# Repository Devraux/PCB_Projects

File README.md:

# PCB sample projects
This repository contains my PCB designs made in KiCad and Altium designer. 
In some cases there is no silkscreen - this is caused by our custom fabrication methods.
In some cases there are "huge" vias - this is caused by our custom(handmoade) fabrication via methods

# Signal Sniffer
|  |  |
|------------------------------------------------------------|-------------------------------------------------------------|
|  |  |

# STM32 Distance sensor
|  |  |
|------------------------------------------------------------|-------------------------------------------------------------|
|  |  |

# Analog multiplier
|  |  |
|------------------------------------------------------------|-------------------------------------------------------------|
|  |  |

# Clock buffer & signal translator
|  |  |
|------------------------------------------------------------|-------------------------------------------------------------|

# Raspberry Pi Pico PIO Signal sniffer
|  |  |
|------------------------------------------------------------|-------------------------------------------------------------|

# HDMI FPGA PMOD adapter
|  |  |
|------------------------------------------------------------|-------------------------------------------------------------|

# Raspberry Pi Pico - Digital probe with HDMI adapter
|  |  |
|------------------------------------------------------------|-------------------------------------------------------------|

|  |  |
|------------------------------------------------------------|-------------------------------------------------------------|

# FPGA ZYNQ Clock TDC
|  |  |
|------------------------------------------------------------|-------------------------------------------------------------|

|  |  |
|------------------------------------------------------------|-------------------------------------------------------------|

|  |  |
|------------------------------------------------------------|-------------------------------------------------------------|

# FPGA RJ11 adapter with RS232 translator
|  |  |
|------------------------------------------------------------|-------------------------------------------------------------|

# Clock signal splitter(2 x 12)
|  |  |
|------------------------------------------------------------|-------------------------------------------------------------|

|  |  |
|------------------------------------------------------------|-------------------------------------------------------------|

# Clock signal splitter(2 x 16)
|  |  |
|------------------------------------------------------------|-------------------------------------------------------------|

|  |  |
|------------------------------------------------------------|-------------------------------------------------------------|

|  |  |
|------------------------------------------------------------|-------------------------------------------------------------|

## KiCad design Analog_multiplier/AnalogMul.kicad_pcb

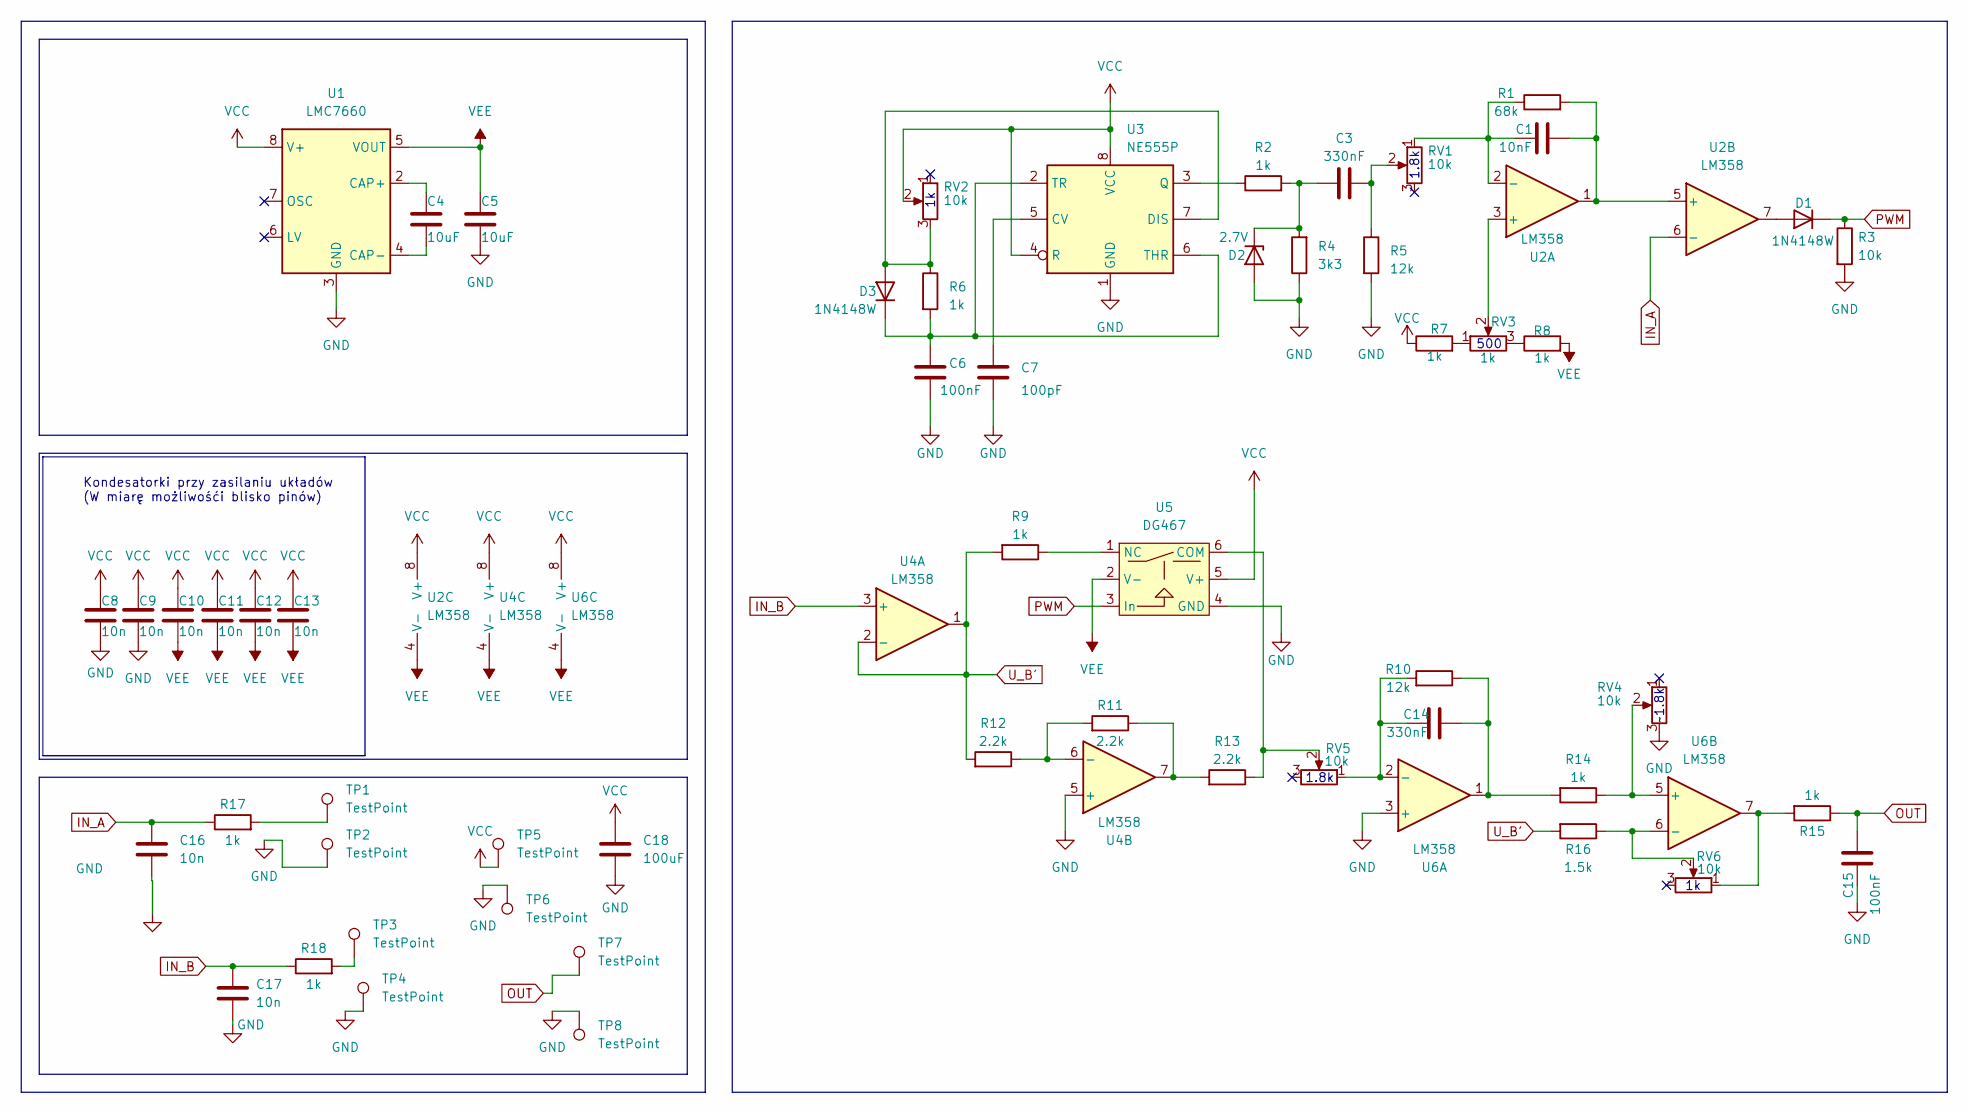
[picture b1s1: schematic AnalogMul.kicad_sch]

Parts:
C1: 10nF; C_0805_2012Metric_Pad1.18x1.45mm_HandSolder
C3, C14: 330nF; C_0805_2012Metric_Pad1.18x1.45mm_HandSolder
C4, C5: 10uF; C_1206_3216Metric
C6, C15: 100nF; C_0805_2012Metric_Pad1.18x1.45mm_HandSolder
C7: 100pF; C_0805_2012Metric_Pad1.18x1.45mm_HandSolder
C8, C9, C10, C11, C12, C13, C16, C17: 10n; C_0805_2012Metric_Pad1.18x1.45mm_HandSolder
C18: 100uF; C_1206_3216Metric
D1, D3: 1N4148W; D_SOD-523
D2: 2.7V; D_SOD-523
R1: 68k; R_0805_2012Metric_Pad1.20x1.40mm_HandSolder
R2, R6, R7, R8, R9, R14, R15, R17, R18: 1k; R_0805_2012Metric_Pad1.20x1.40mm_HandSolder
R3: 10k; R_0805_2012Metric_Pad1.20x1.40mm_HandSolder
R4: 3k3; R_0805_2012Metric_Pad1.20x1.40mm_HandSolder
R5, R10: 12k; R_0805_2012Metric_Pad1.20x1.40mm_HandSolder
R11, R12, R13: 2.2k; R_0805_2012Metric_Pad1.20x1.40mm_HandSolder
R16: 1.5k; R_0805_2012Metric_Pad1.20x1.40mm_HandSolder
RV1, RV2, RV4, RV5, RV6: 10k; Potentiometer_Runtron_RM-063_Horizontal
RV3: 1k; Potentiometer_Runtron_RM-063_Horizontal
TP1, TP2, TP3, TP4, TP5, TP6, TP7, TP8: TestPoint; TestPoint_Loop_D1.80mm_Drill1.0mm_Beaded
U1: LMC7660; SO-8_3.9x4.9mm_P1.27mm
U2, U4, U6: LM358; SO-8_3.9x4.9mm_P1.27mm
U3: NE555P; SO-8_3.9x4.9mm_P1.27mm
U5: DG467; SOT-23-6

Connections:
GND: C5.1, C6.2, C7.2, C8.2, C9.2, C15.1, C16.2, C17.1, C18.2, D2.2 (A), R3.2, R4.1, R5.2, RV4.3, TP2.1, TP4.1, TP6.1, TP8.1, U1.3 (GND), U3.1 (GND), U4.5 (+), U5.4 (GND), U6.3 (+)
IN_A: C16.1, R17.1, U2.6 (-)
IN_B: C17.2, R18.1, U4.3 (+)
unnamed: C3.2, R5.1, RV1.2
unnamed: C14.2, R10.1, R14.2, U6.1
unnamed: D1.2 (A), U2.7
unnamed: C3.1, D2.1 (K), R2.2, R4.2
unnamed: D3.2 (A), R6.1, RV2.3, U3.7 (DIS)
unnamed: C6.1, D3.1 (K), R6.2, U3.2 (TR), U3.6 (THR)
unnamed: R7.2, RV3.1
unnamed: R8.1, RV3.3
unnamed: R11.1, R13.2, U4.7
unnamed: R15.2, RV6.1, U6.7
unnamed: R17.2, TP1.1
unnamed: R18.2, TP3.1
unnamed: C4.1, U1.2 (CAP+)
unnamed: C4.2, U1.4 (CAP-)
unnamed: RV3.2, U2.3 (+)
unnamed: C1.1, R1.1, RV1.1, U2.2 (-)
unnamed: C1.2, R1.2, U2.1, U2.5 (+)
unnamed: C7.1, U3.5 (CV)
unnamed: R2.1, U3.3 (Q)
unnamed: R11.2, R12.1, U4.6 (-)
unnamed: R13.1, RV5.2, U5.6 (COM)
unnamed: R9.1, U5.1 (NC)
unnamed: C14.1, R10.2, RV5.1, U6.2 (-)
unnamed: R14.1, RV4.2, U6.5 (+)
unnamed: R16.1, RV6.2, U6.6 (-)
OUT: C15.2, R15.1, TP7.1
PWM: D1.1 (K), R3.1, U5.3 (In)
U_B': R9.2, R12.2, R16.2, U4.1, U4.2 (-)
VCC: C8.1, C9.1, C10.1, C11.1, C12.1, C13.1, C18.1, R7.1, RV2.2, TP5.1, U1.8 (V+), U2.8 (V+), U3.4 (R), U3.8 (VCC), U4.8 (V+), U5.5 (V+), U6.8 (V+)
VEE: C5.2, C10.2, C11.2, C12.2, C13.2, R8.2, U1.5 (VOUT), U2.4 (V-), U4.4 (V-), U5.2 (V-), U6.4 (V-)

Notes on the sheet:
~1.8k
Kondesatorki przy zasilaniu układów (W miarę możliwośći blisko pinów)
1.8k
500

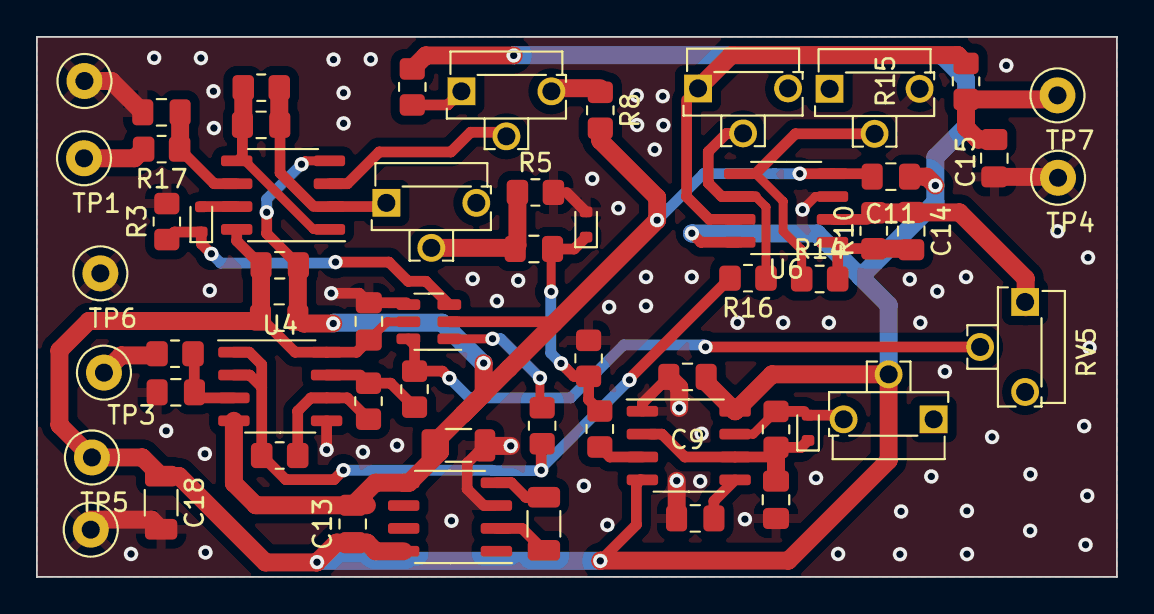
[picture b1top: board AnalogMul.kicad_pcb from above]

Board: 2 copper layers, 60.0 x 30.0 mm, 58 parts (0 on the bottom side), 33 nets.

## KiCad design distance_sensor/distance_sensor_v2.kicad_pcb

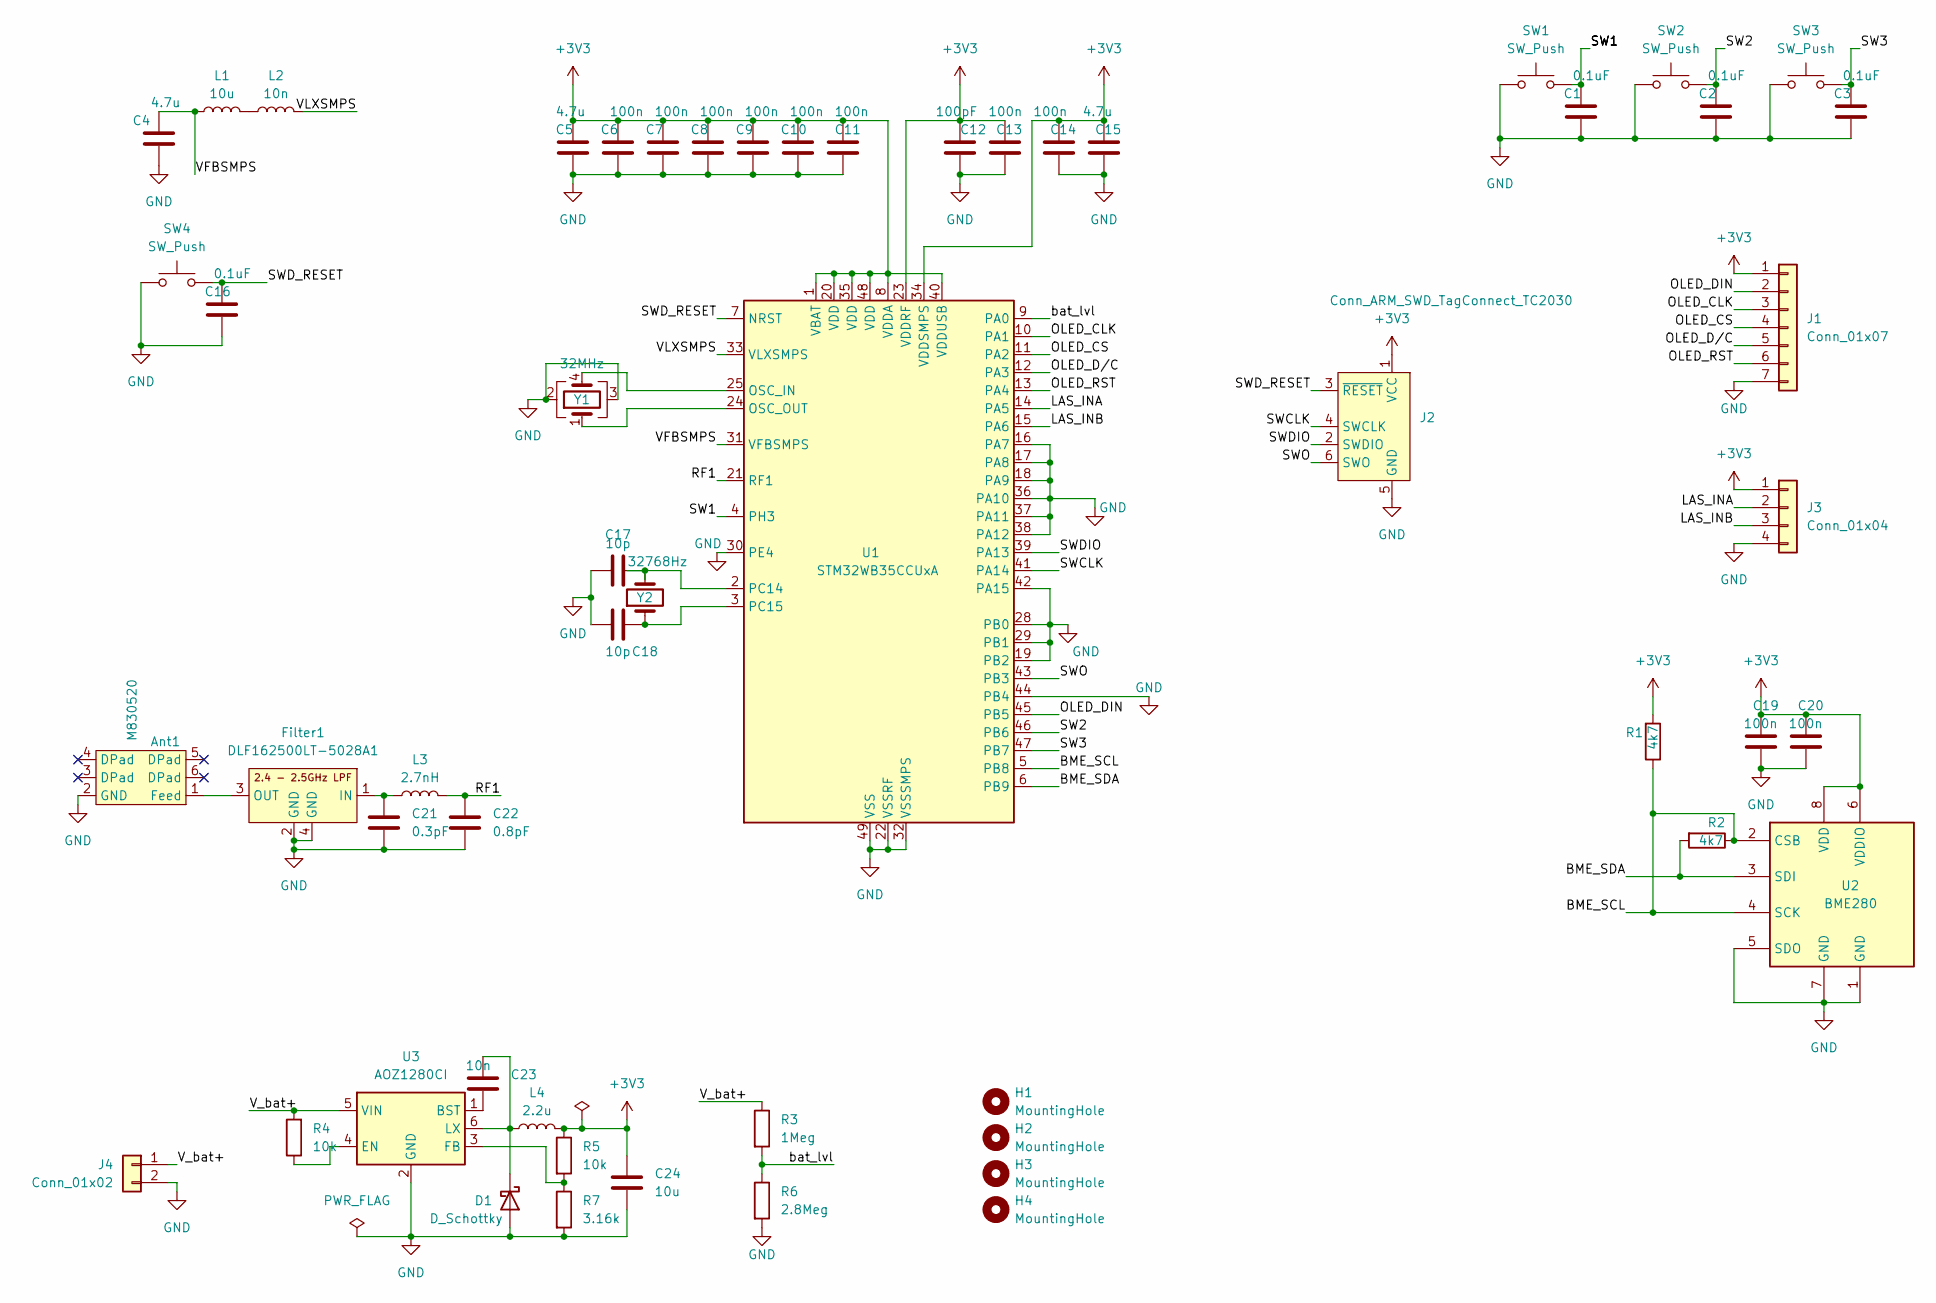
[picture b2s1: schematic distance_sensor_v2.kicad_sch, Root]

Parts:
Ant1: M830520
C1, C2, C3, C16: 0.1uF; C_0603_1608Metric
C4, C15: 4.7u; C_0603_1608Metric
C5: 4.7u; C_0402_1005Metric
C6, C9, C11, C13: 100n; C_0402_1005Metric
C7, C8, C10, C14, C19, C20: 100n; C_0603_1608Metric
C12: 100pF; C_0402_1005Metric
C17, C18: 10p; C_0603_1608Metric
C21: 0.3pF; C_0402_1005Metric
C22: 0.8pF; C_0402_1005Metric
C23: 10n; C_0603_1608Metric
C24: 10u; C_0603_1608Metric
D1: D_Schottky; D_SOD-323
Filter1: DLF162500LT-5028A1
H1, H2, H3, H4: MountingHole; MountingHole_2.1mm
J1: Conn_01x07; Molex_PicoBlade_53261-0771_1x07-1MP_P1.25mm_Horizontal
J2: Conn_ARM_SWD_TagConnect_TC2030; Tag-Connect_TC2030-IDC-FP_2x03_P1.27mm_Vertical
J3: Conn_01x04; Molex_PicoBlade_53261-0471_1x04-1MP_P1.25mm_Horizontal
J4: Conn_01x02; Molex_PicoBlade_53048-0210_1x02_P1.25mm_Horizontal
L1: 10u; L_0603_1608Metric
L2: 10n; L_0603_1608Metric
L3: 2.7nH; L_0402_1005Metric
L4: 2.2u; L_0603_1608Metric
R1, R2: 4k7; R_0603_1608Metric
R3: 1Meg; R_0603_1608Metric
R4, R5: 10k; R_0603_1608Metric
R6: 2.8Meg; R_0603_1608Metric
R7: 3.16k; R_0603_1608Metric
SW1, SW2, SW3: SW_Push; SW_PUSH_6mm
SW4: SW_Push; SW_SPST_FSMSM
U1: STM32WB35CCUxA; QFN-48-1EP_7x7mm_P0.5mm_EP5.6x5.6mm
U2: BME280; Bosch_LGA-8_2.5x2.5mm_P0.65mm_ClockwisePinNumbering
U3: AOZ1280CI; SOT-23-6
Y1: 32MHz; Crystal_SMD_2016-4Pin_2.0x1.6mm
Y2: 32768Hz; Crystal_SMD_2012-2Pin_2.0x1.2mm

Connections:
+3V3: C5.1, C6.1, C7.1, C8.1, C9.1, C10.1, C11.1, C12.1, C13.1, C14.1, C15.1, C19.1, C20.1, C24.1, J1.1, J2.1 (VCC), J3.1, L4.2, R1.2, R5.1, U1.1 (VBAT), U1.8 (VDDA), U1.20 (VDD), U1.23 (VDDRF), U1.34 (VDDSMPS), U1.35 (VDD), U1.40 (VDDUSB), U1.48 (VDD), U2.6 (VDDIO), U2.8 (VDD)
/BME_SCL: R1.1, R2.1, U1.5 (PB8), U2.2 (CSB), U2.4 (SCK)
/BME_SDA: R2.2, U1.6 (PB9), U2.3 (SDI)
/LAS_INA: J3.2, U1.14 (PA5)
/LAS_INB: J3.3, U1.15 (PA6)
/OLED_CLK: J1.3, U1.10 (PA1)
/OLED_CS: J1.4, U1.11 (PA2)
/OLED_DIN: J1.2, U1.45 (PB5)
/OLED_D/C: J1.5, U1.12 (PA3)
/OLED_RST: J1.6, U1.13 (PA4)
/RF1: C22.1, L3.2, U1.21 (RF1)
/SW1: C1.2, SW1.2, U1.4 (PH3)
/SW2: C2.2, SW2.2, U1.46 (PB6)
/SW3: C3.2, SW3.2, U1.47 (PB7)
/SWCLK: J2.4 (SWCLK), U1.41 (PA14)
/SWDIO: J2.2 (SWDIO), U1.39 (PA13)
/SWD_RESET: C16.2, J2.3 (~RESET), SW4.2, U1.7 (NRST)
/SWO: J2.6 (SWO), U1.43 (PB3)
/VFBSMPS: C4.1, L1.1, U1.31 (VFBSMPS)
/VLXSMPS: L2.2, U1.33 (VLXSMPS)
/V_bat+: J4.1, R3.1, R4.2, U3.5 (VIN)
/bat_lvl: R3.2, R6.1, U1.9 (PA0)
GND: Ant1.2 (GND), C1.1, C2.1, C3.1, C4.2, C5.2, C6.2, C7.2, C8.2, C9.2, C10.2, C11.2, C12.2, C13.2, C14.2, C15.2, C16.1, C17.1, C18.1, C19.2, C20.2, C21.2, C22.2, C24.2, D1.2 (A), J1.7, J2.5 (GND), J3.4, J4.2, R6.2, R7.2, SW1.1, SW2.1, SW3.1, SW4.1, U1.16 (PA7), U1.17 (PA8), U1.18 (PA9), U1.19 (PB2), U1.22 (VSSRF), U1.28 (PB0), U1.29 (PB1), U1.30 (PE4), U1.32 (VSSSMPS), U1.36 (PA10), U1.37 (PA11), U1.38 (PA12), U1.42 (PA15), U1.44 (PB4), U1.49 (VSS), U2.1 (GND), U2.5 (SDO), U2.7 (GND), U3.2 (GND), Y1.2, Y1.3; also elsewhere on the board
unnamed 23: Ant1.1 (Feed), Filter1.3 (OUT); also elsewhere on the board
unnamed: C23.2, D1.1 (K), L4.1, U3.6 (LX)
unnamed 25: C21.1, L3.1; also elsewhere on the board
unnamed: L1.2, L2.1
unnamed: U1.25 (OSC_IN), Y1.4
unnamed: U1.24 (OSC_OUT), Y1.1
unnamed: C17.2, U1.2 (PC14), Y2.2
unnamed: C18.2, U1.3 (PC15), Y2.1
unnamed: C23.1, U3.1 (BST)
unnamed: R4.1, U3.4 (EN)
unnamed: R5.2, R7.1, U3.3 (FB)

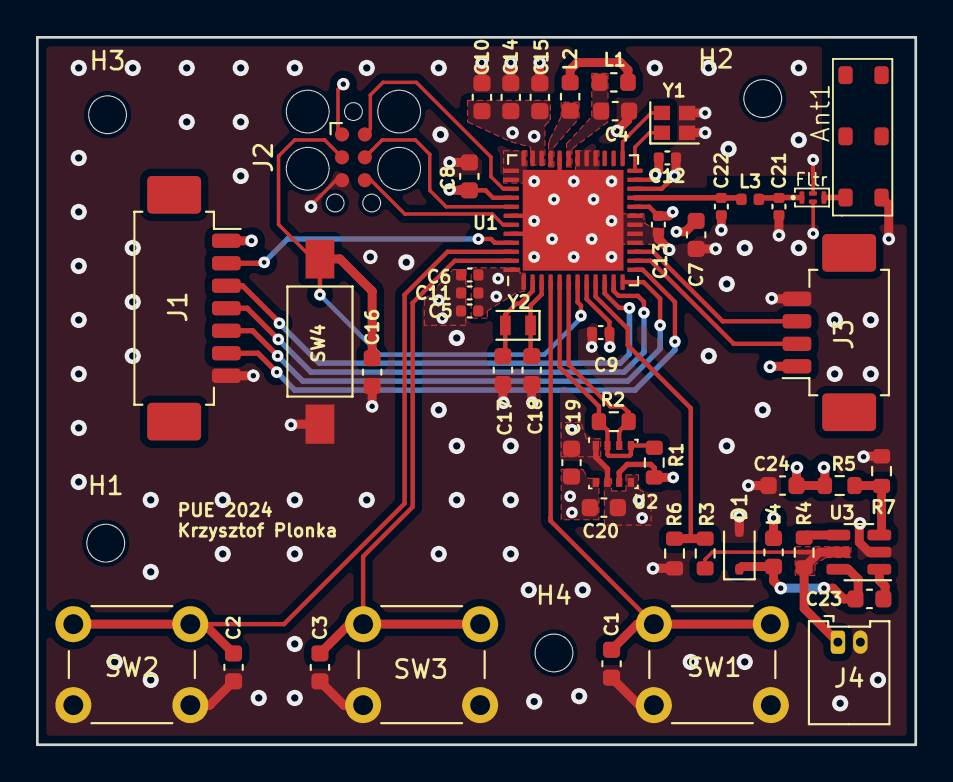
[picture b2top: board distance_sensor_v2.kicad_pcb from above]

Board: 4 copper layers, 48.8 x 39.3 mm, 55 parts (0 on the bottom side), 34 nets.

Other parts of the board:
Fltr: DLF162500LT-5028A1

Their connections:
GND: Fltr.2 (GND), Fltr.4 (GND); also elsewhere on the board
unnamed 23: Fltr.3 (OUT); also elsewhere on the board
unnamed 25: Fltr.1 (IN); also elsewhere on the board

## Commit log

2025-01-26 distance_measure_device
2025-01-26 Signal_sniffer
2025-01-26 Analog multipler
2025-01-26 PM_PCB_Adapter
